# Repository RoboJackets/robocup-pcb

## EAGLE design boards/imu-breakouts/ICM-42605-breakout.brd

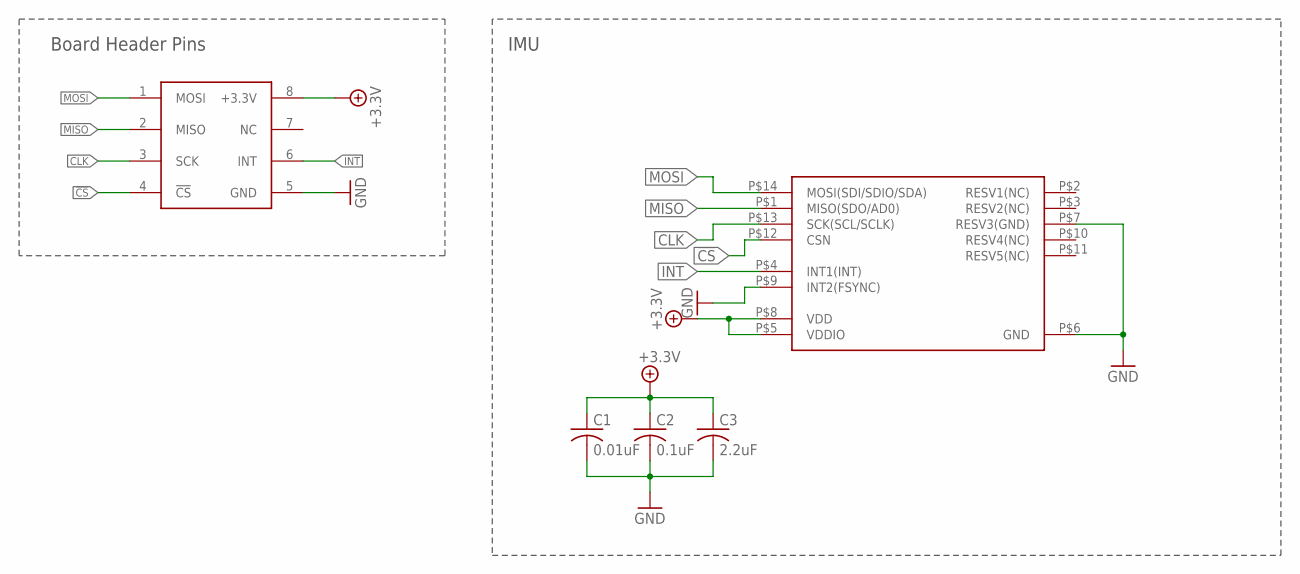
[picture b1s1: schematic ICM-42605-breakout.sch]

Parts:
C1: 0.01uF; C0603
C2: 0.1uF; C0603
C3: 2.2uF; C0603
KIT1: IMUIMU-KIT; IMU-KIT
U3: ICM-42605; ICM-442605-2530091

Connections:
!CS!: KIT1.4 (!CS!), U3.P$12 (CSN)
+3.3V: C1.1, C2.1, C3.1, KIT1.8 (+3.3V), U3.P$5 (VDDIO), U3.P$8 (VDD)
CLK: KIT1.3 (SCK), U3.P$13 (SCK(SCL/SCLK))
GND: C1.2, C2.2, C3.2, KIT1.5 (GND), U3.P$6 (GND), U3.P$7 (RESV3(GND)), U3.P$9 (INT2(FSYNC))
INT: KIT1.6 (INT), U3.P$4 (INT1(INT))
MISO: KIT1.2 (MISO), U3.P$1 (MISO(SDO/AD0))
MOSI: KIT1.1 (MOSI), U3.P$14 (MOSI(SDI/SDIO/SDA))

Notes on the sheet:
IMU
Board Header Pins

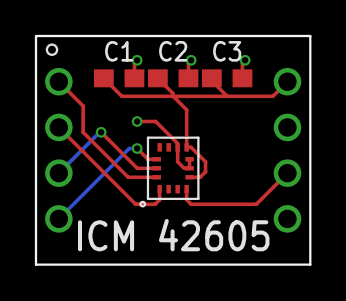
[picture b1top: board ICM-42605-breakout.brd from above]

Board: 2 copper layers, 15.2 x 12.7 mm, 5 parts (0 on the bottom side), 7 nets.

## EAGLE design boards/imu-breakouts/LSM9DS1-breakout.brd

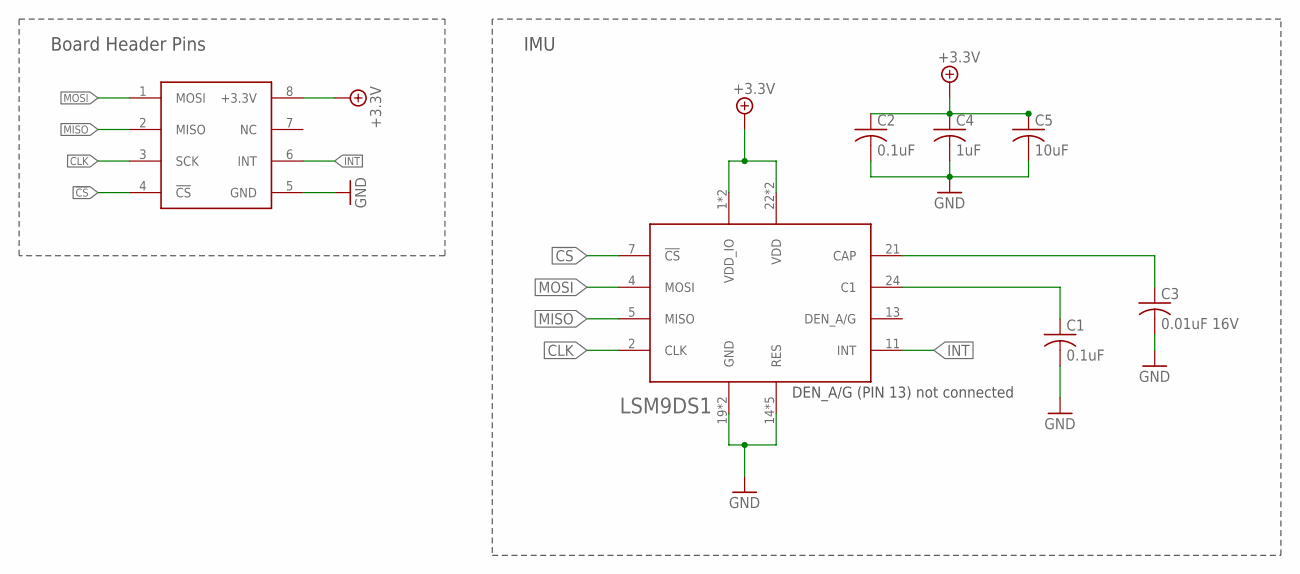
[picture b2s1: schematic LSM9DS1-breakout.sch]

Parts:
C1, C2: 0.1uF; C0603
C3: 0.01uF 16V; C0603
C4: 1uF; C0603
C5: 10uF; C0603
KIT1: IMUIMU-KIT; IMU-KIT
U1: LSM9DS1; LGA-24L

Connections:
!CS!: KIT1.4 (!CS!), U1.7 (!CS!)
+3.3V: C2.1, C4.1, C5.1, KIT1.8 (+3.3V), U1.1 (VDD_IO), U1.3 (VDD_IO), U1.22 (VDD), U1.23 (VDD)
C1: C1.1, U1.24 (C1)
CAP: C3.1, U1.21 (CAP)
CLK: KIT1.3 (SCK), U1.2 (CLK)
GND: C1.2, C2.2, C3.2, C4.2, C5.2, KIT1.5 (GND), U1.14 (RES), U1.15 (RES), U1.16 (RES), U1.17 (RES), U1.18 (RES), U1.19 (GND), U1.20 (GND)
INT: KIT1.6 (INT), U1.11 (INT)
MISO: KIT1.2 (MISO), U1.5 (MISO)
MOSI: KIT1.1 (MOSI), U1.4 (MOSI)

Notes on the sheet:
IMU
Board Header Pins
DEN_A/G (PIN 13) not connected

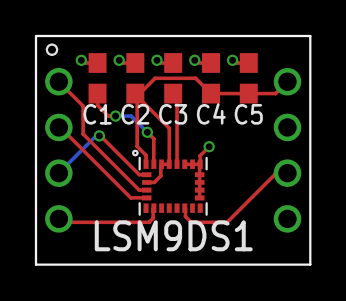
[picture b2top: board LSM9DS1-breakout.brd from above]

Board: 2 copper layers, 15.2 x 12.7 mm, 7 parts (0 on the bottom side), 9 nets.

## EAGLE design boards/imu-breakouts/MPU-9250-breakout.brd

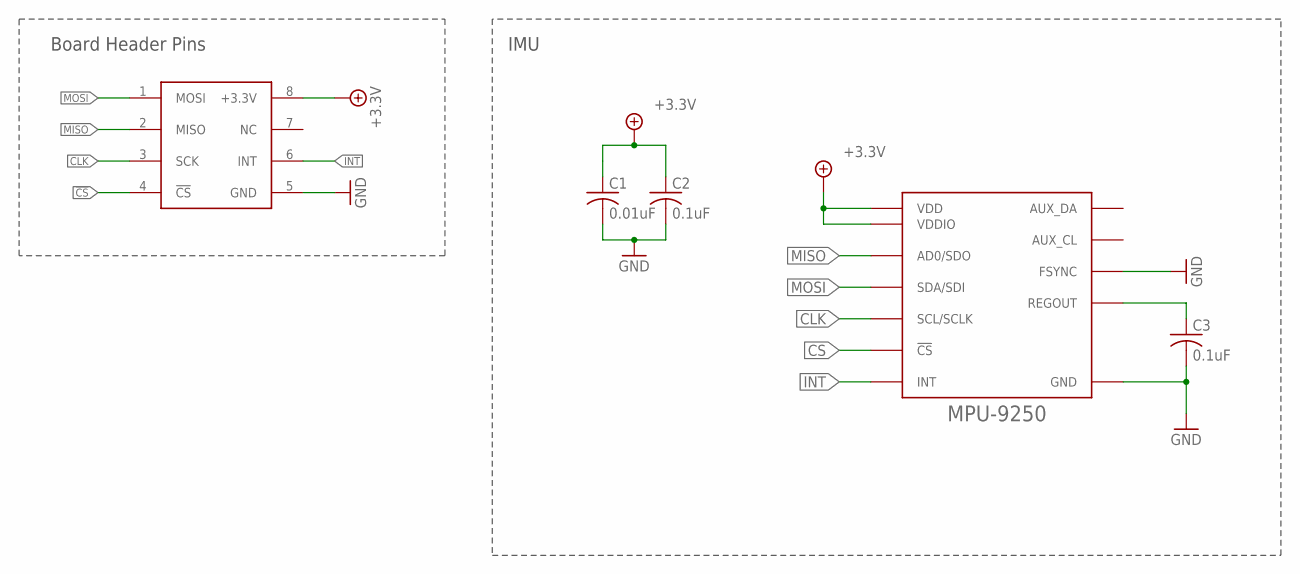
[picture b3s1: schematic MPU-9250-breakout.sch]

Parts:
C1: 0.01uF; C0603
C2, C3: 0.1uF; C0603
IC1: MPU-9250; QFN-24-4MM2
KIT1: IMUIMU-KIT; IMU-KIT

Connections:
!CS!: KIT1.4 (!CS!)
+3.3V: C1.1, C2.1, IC1.1 (VDDIO), IC1.8 (VDDIO), IC1.13 (VDD), KIT1.8 (+3.3V)
CLK: IC1.23 (SCL/SCLK), KIT1.3 (SCK)
CS: IC1.22 (!CS!)
GND: C1.2, C2.2, C3.2, IC1.11 (FSYNC), IC1.18 (GND), IC1.20 (GND), KIT1.5 (GND)
INT: IC1.12 (INT), KIT1.6 (INT)
MISO: IC1.9 (AD0/SDO), KIT1.2 (MISO)
MOSI: IC1.24 (SDA/SDI), KIT1.1 (MOSI)
unnamed: C3.1, IC1.10 (REGOUT)

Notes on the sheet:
IMU
Board Header Pins

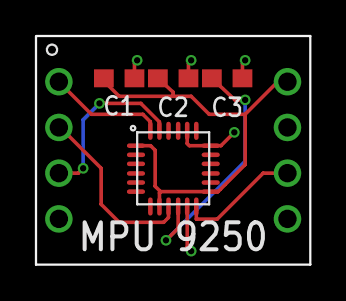
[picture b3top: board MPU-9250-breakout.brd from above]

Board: 2 copper layers, 15.2 x 12.7 mm, 5 parts (0 on the bottom side), 7 nets.

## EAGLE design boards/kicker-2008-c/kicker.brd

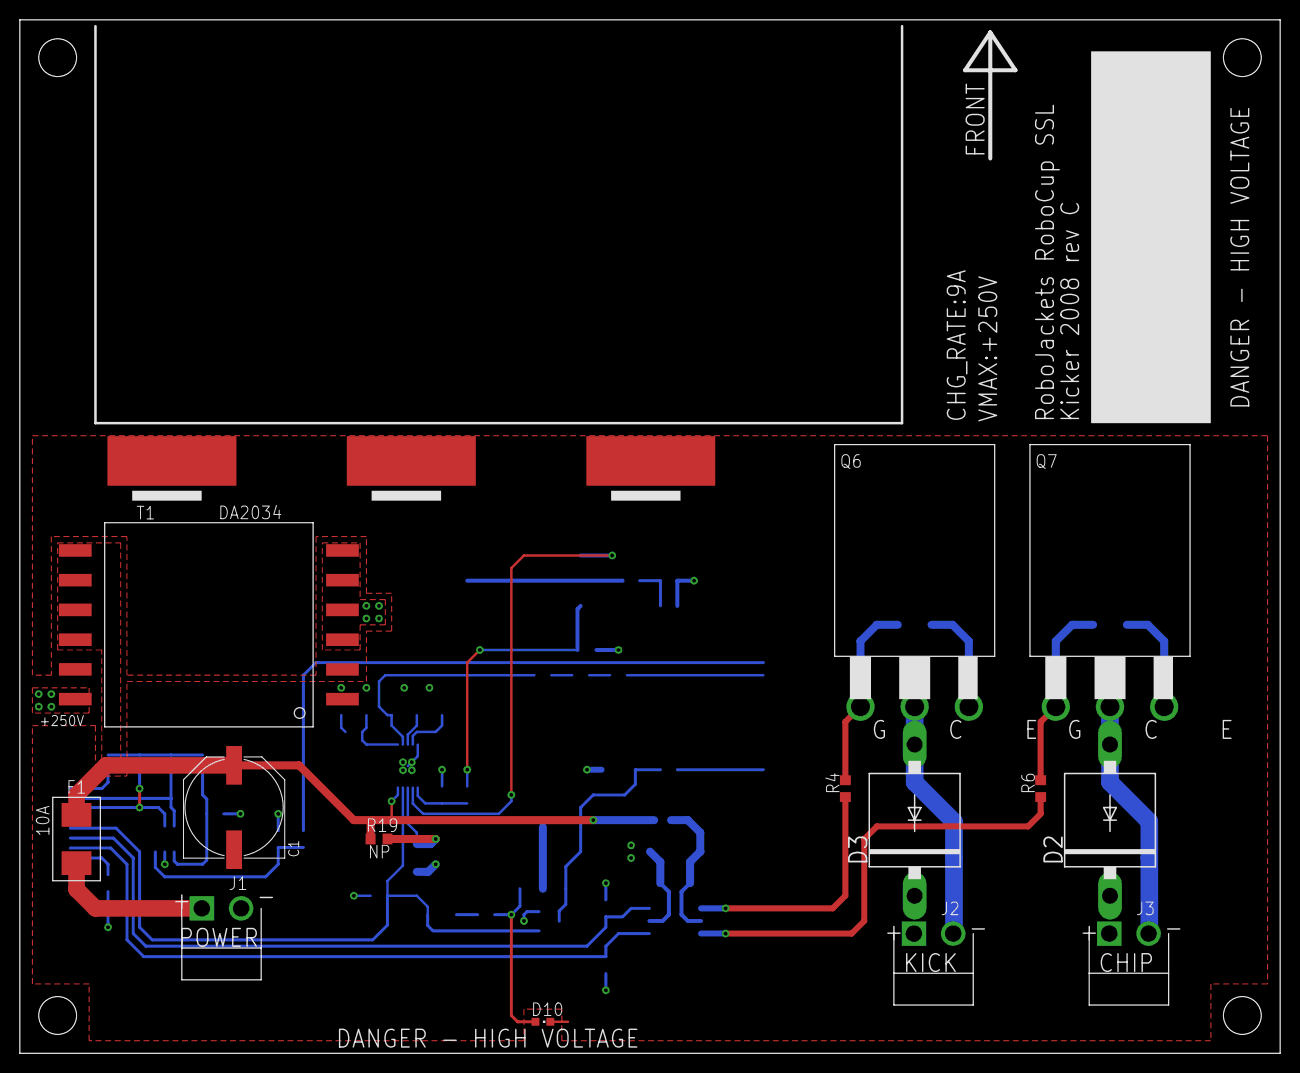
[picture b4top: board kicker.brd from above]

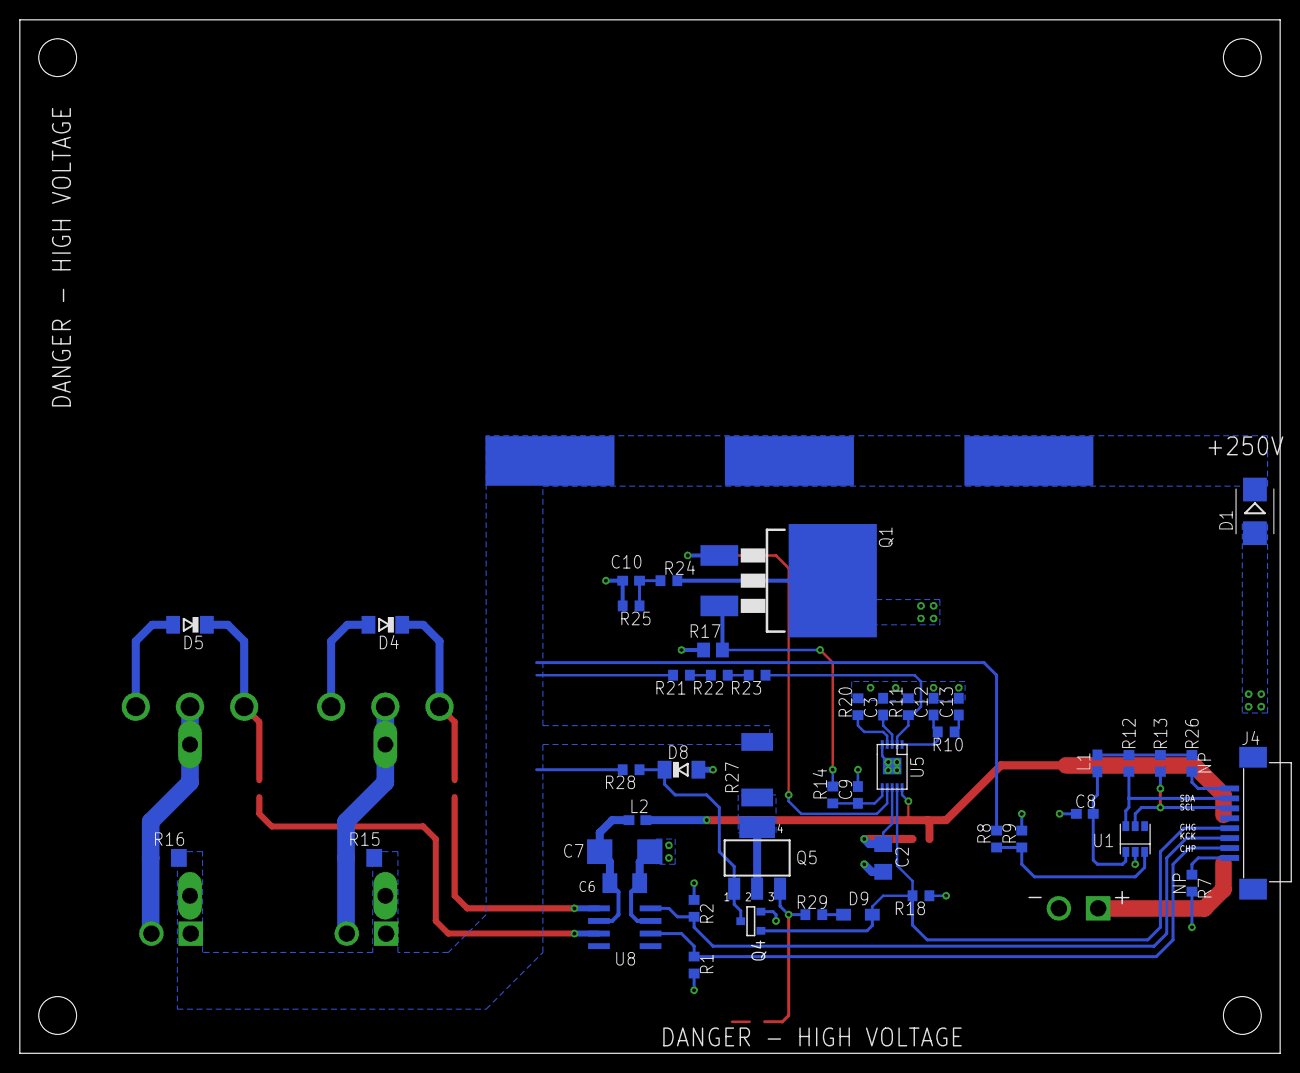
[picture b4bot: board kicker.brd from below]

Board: 2 copper layers, 127.0 x 104.1 mm, 64 parts (47 on the bottom side), 39 nets.

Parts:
C1: UWT1E471MNL1GS; PANASONIC_G
C2: 4.7uF, 25v; C1206
C3, C8: 100nF; C0603
C6: 4.7uF; C1206K
C7: 47uF; C/6032-28R
C9, C13: 22nF; C0603
C10: 220pF 100V; C0603
C12: 100pF; C0603
D1: STTH3R06U; SMB
D2, D3: 6A6-T; P6-15
D4, D5, D8: BZV55-B18,115; SOD80C
D9: BAS16H; SOD323-W
D10: LTST-S270KRKT; CHIPLED_0603
F1: 10A; NANO2_157
J1: POWER; JST_VH_2_RA
J2: KICK_R; JST_VH_2_RA
J3: KICK_L; JST_VH_2_RA
J4: 0528520870
L1, L2: HZ0603B102R-10; C0603
Q1: STB40NF20; D2PACK
Q4: FDV303N; SOT-23
Q5: FQT1N80; SOT223
Q6, Q7: IXGX400N30A3; PLUS247
R1, R2, R9, R12, R13, R18: 10.0k; R0603
R4, R6: 10; R0603
R7, R19, R25, R26: NP; R0603
R8: 1.00M; R0603
R10: 6.8k; R0603
R11: 16.20k, 1% (MCR03EZPFX1622); R0603
R14, R24: 22; R0603
R15, R16: 680K; R1206
R17: 0.015 (ERJ-6BWFR015V); R0805
R20: 140k; R0603
R21: 470k 1%; R0603
R22, R23: 1.00M, 1% (MCR03EZPFX1004); R0603
R27: RHC2512FT33K0; R2512
R28: 10M; R0603
R29: 220; R0603
T1: DA2034
U1: ADC081C027; SOT23-6
U5: LT3757; MSOP-10-MSE
U8: TC4427; SO08
U$3, U$4, U$5: EET-UQ2E821CA; 22CAP

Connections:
+3V3: L1.1, R12.2, R13.2, R26.2
+12V: C1.+, F1.P$2, L2.2, R19.1, T1.7, T1.8, T1.9, T1.10, U5.10
CHARGE: D9.A, J4.4, Q4.3, R18.2, U5.9
CHIP: J4.2, R1.2, U8.2
GND: C1.-, C2.2, C3.2, C6.2, C7.-, C8.2, C9.2, C10.2, C12.2, C13.2, D4.A, D5.A, D8.A, D10.C, J1.2, Q4.2, Q6.P$3, Q7.P$3, R1.1, R2.1, R7.2, R9.1, R11.1, R17.1, R18.1, R20.2, R25.1, T1.1, U1.2, U5.5, U5.11, U8.3, U$3.2, U$4.2, U$5.2
HV: D1.C, D2.C, D3.C, J2.1, J3.1, R8.2, R15.2, R16.2, R21.2, R27.2, R28.2, U$3.1, U$4.1, U$5.1
KICK: J4.3, R2.2, U8.4
unnamed: D5.C, Q7.P$1, R6.2
unnamed: Q1.1, U5.7
unnamed: J4.1, R7.1
unnamed: C12.1, R10.1, U5.1
unnamed: C13.1, R10.2
unnamed: R22.1, R23.2
unnamed: D4.C, Q6.P$1, R4.2
unnamed: R8.1, R9.2, U1.3
unnamed: D2.A, J3.2, Q7.P$2, R16.1
unnamed: J4.8, R26.1
unnamed: R4.1, U8.5
unnamed: R6.1, U8.7
unnamed: D3.A, J2.2, Q6.P$2, R15.1
unnamed: C6.1, C7.+, L2.1, U8.6
unnamed: C8.1, L1.2, U1.1
unnamed: D8.C, Q4.1, Q5.1, R28.1
unnamed: Q5.2, Q5.4, R27.1
unnamed: R21.1, R22.2
unnamed: R11.2, R23.1, U5.2
unnamed: F1.P$1, J1.1
unnamed: Q1.2, R24.2, T1.3, T1.4, T1.5, T1.6
unnamed: C3.1, U5.3
unnamed: R20.1, U5.4
unnamed: C2.1, R19.2, U5.8
unnamed: D10.A, Q5.3, R29.2
unnamed: C9.1, R14.1, U5.6
unnamed: C10.1, R24.1, R25.2
unnamed: D9.C, R29.1
unnamed: D1.A, T1.12
NAG: Q1.3, R14.2, R17.2
SCL: J4.6, R13.1, U1.5
SDA: J4.7, R12.1, U1.6
